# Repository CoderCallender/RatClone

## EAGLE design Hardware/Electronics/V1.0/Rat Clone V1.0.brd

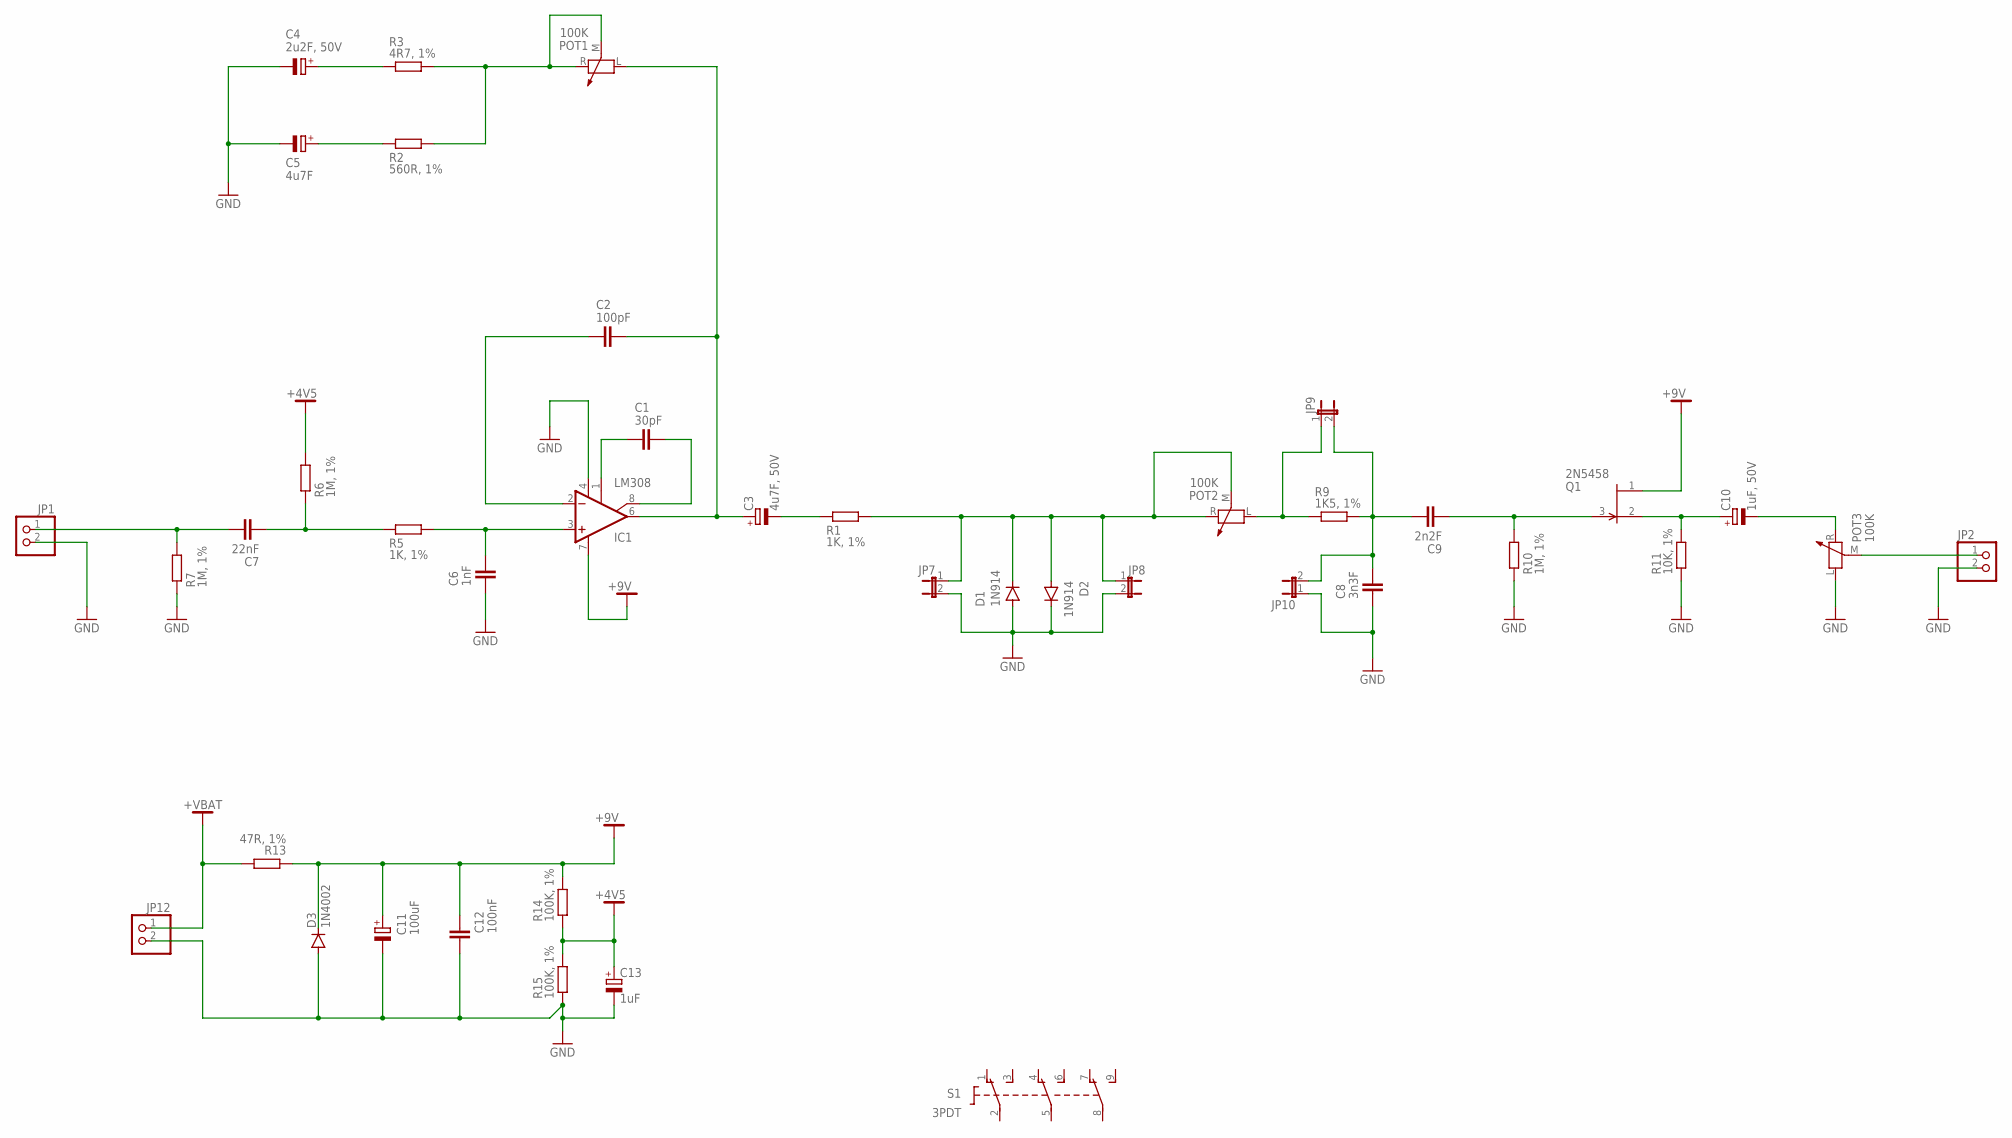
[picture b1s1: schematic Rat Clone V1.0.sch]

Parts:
C1: 30pF; C025-025X050; MPN C315C300J3G5TA
C2: 100pF; C025-025X050; MPN K101J15C0GF5TL2
C3: 4u7F, 50V; E2,5-6; MPN MCGPR50V475M5X11
C4: 2u2F, 50V; E2,5-6; MPN MCMR50V225M4X7
C5: 4u7F; E2,5-6; MPN MCMR50V475M4X7
C6: 1nF; C025-025X050; MPN R82EC1100DQ50J
C7: 22nF; C050-025X075; MPN R82EC2220DQ50JB
C8: 3n3F; C025-025X050; MPN R82EC1330DQ50JB
C9: 2n2F; C025-025X050; MPN C242A222J20C450
C10: 1uF, 50V; E2,5-6; MPN MCGPR50V105M5X11
C11: 100uF; E2,5-5; MPN ESK107M016AC3AA
C12: 100nF; C025-025X050; MPN R82EC3100DQ70JB
C13: 1uF; E2,5-6; MPN MCGPR50V105M5X11
D1, D2: 1N914; DO35-10; MPN 1N914
D3: 1N4002; DO41-10; MPN 1N4002G
IC1: LM308; DIL08
JP1, JP2, JP12: PINHD-1X2; 1X02; MPN 20-0134
JP7, JP8, JP9, JP10: JP1E; JP1
POT1, POT2, POT3: 100K; MA03-1
Q1: 2N5458; TO92-
R1, R5: 1K, 1%; 0207/7; MPN MF0W4FF1001KIT
R2: 560R, 1%; 0207/7; MPN MFF04FF5600KIT
R3: 4R7, 1%; 0207/7; MPN MF0W4FF470KKIT
R6, R7, R10: 1M, 1%; 0207/7; MPN MF0W4FF1004KIT
R9: 1K5, 1%; 0207/7; MPN MF0W4FF1501KIT
R11: 10K, 1%; 0207/7; MPN MF0W4FF1002KIT
R13: 47R, 1%; 0207/7; MPN MF006FF470JKIT
R14, R15: 100K, 1%; 0207/7; MPN MF0W4FF1003KIT
S1: 3PDT; MPN SF17020F-0302-21R-L

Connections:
+4V5: C13.+, R6.2, R14.1, R15.2
+9V: C11.+, C12.1, D3.C, IC1.7 (V+), Q1.1 (D), R13.1, R14.2
+VBAT: JP12.1, R13.2
GND: C4.-, C5.-, C6.1, C8.1, C11.-, C12.2, C13.-, D1.A, D2.C, D3.A, IC1.4 (V-), JP1.2, JP2.2, JP7.2, JP8.2, JP10.1, JP12.2, POT3.L (1), R7.1, R10.1, R11.1, R15.1
unnamed: C1.1, IC1.1 (CMP1)
unnamed: C1.2, IC1.8 (CMP2)
unnamed: C3.-, R1.1
unnamed: C2.2, C3.+, IC1.6 (OUT), POT1.L (1)
unnamed: C2.1, IC1.2 (-IN)
unnamed: D1.C, D2.A, JP7.1, JP8.1, POT2.M (3), POT2.R (2), R1.2
unnamed: POT1.M (3), POT1.R (2), R2.2, R3.2
unnamed: C10.+, Q1.2 (S), R11.2
unnamed: C5.+, R2.1
unnamed: JP9.1, POT2.L (1), R9.1
unnamed: C6.2, IC1.3 (+IN), R5.2
unnamed: C7.1, R5.1, R6.1
unnamed: C7.2, JP1.1, R7.2
unnamed: C8.2, C9.2, JP9.2, JP10.2, R9.2
unnamed: C9.1, Q1.3 (G), R10.2
unnamed: C10.-, POT3.R (2)
unnamed: JP2.1, POT3.M (3)
unnamed: C4.+, R3.1

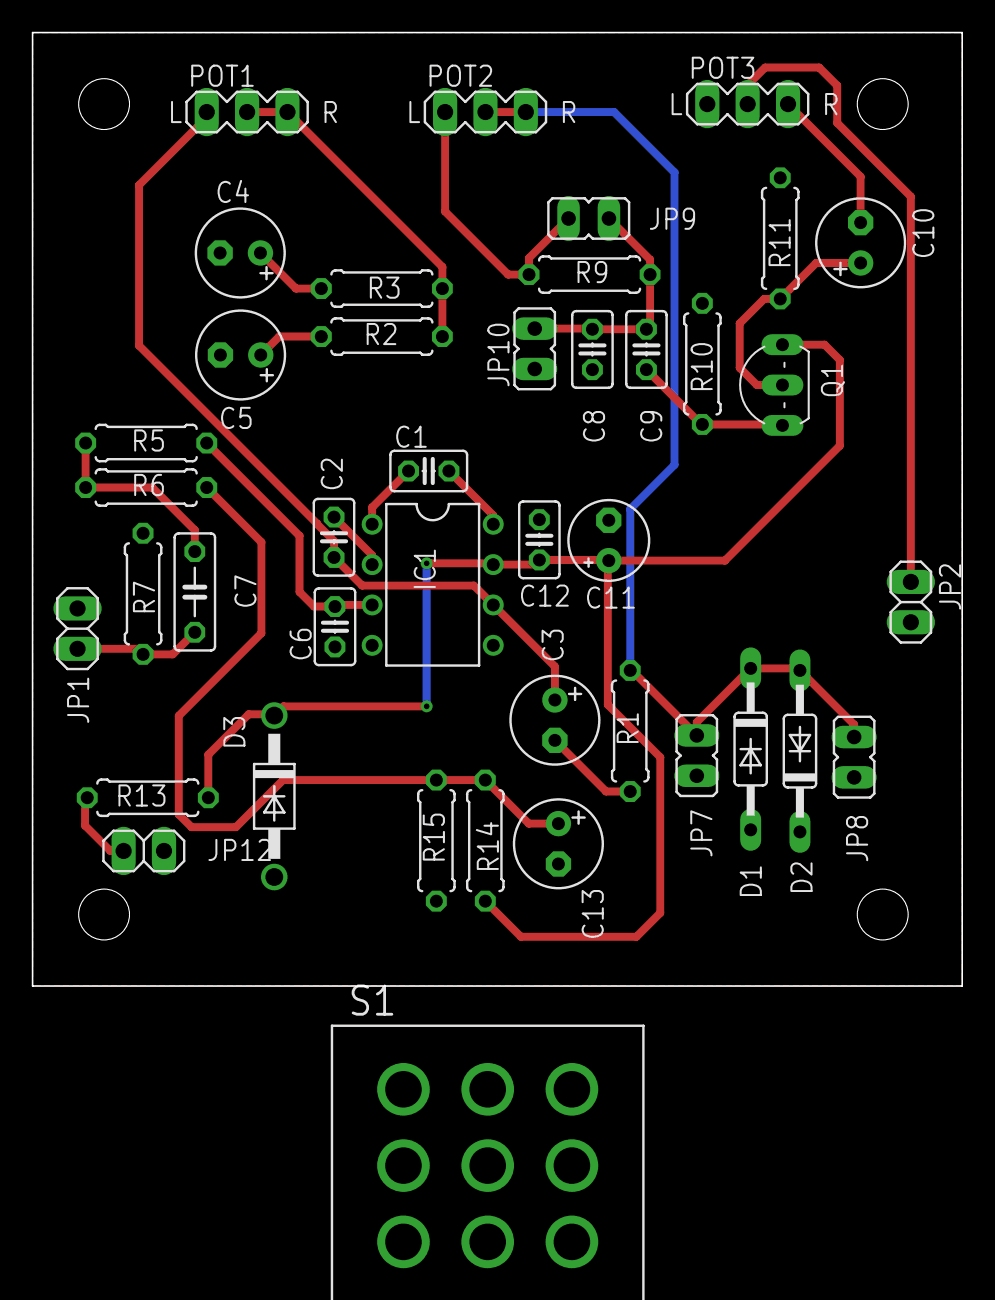
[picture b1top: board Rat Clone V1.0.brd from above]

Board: 2 copper layers, 58.5 x 60.0 mm, 41 parts (0 on the bottom side), 22 nets.

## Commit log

2022-03-23 Moved to screw mounted PCB
    Basic routing
    2 layer same price as 1 layer
